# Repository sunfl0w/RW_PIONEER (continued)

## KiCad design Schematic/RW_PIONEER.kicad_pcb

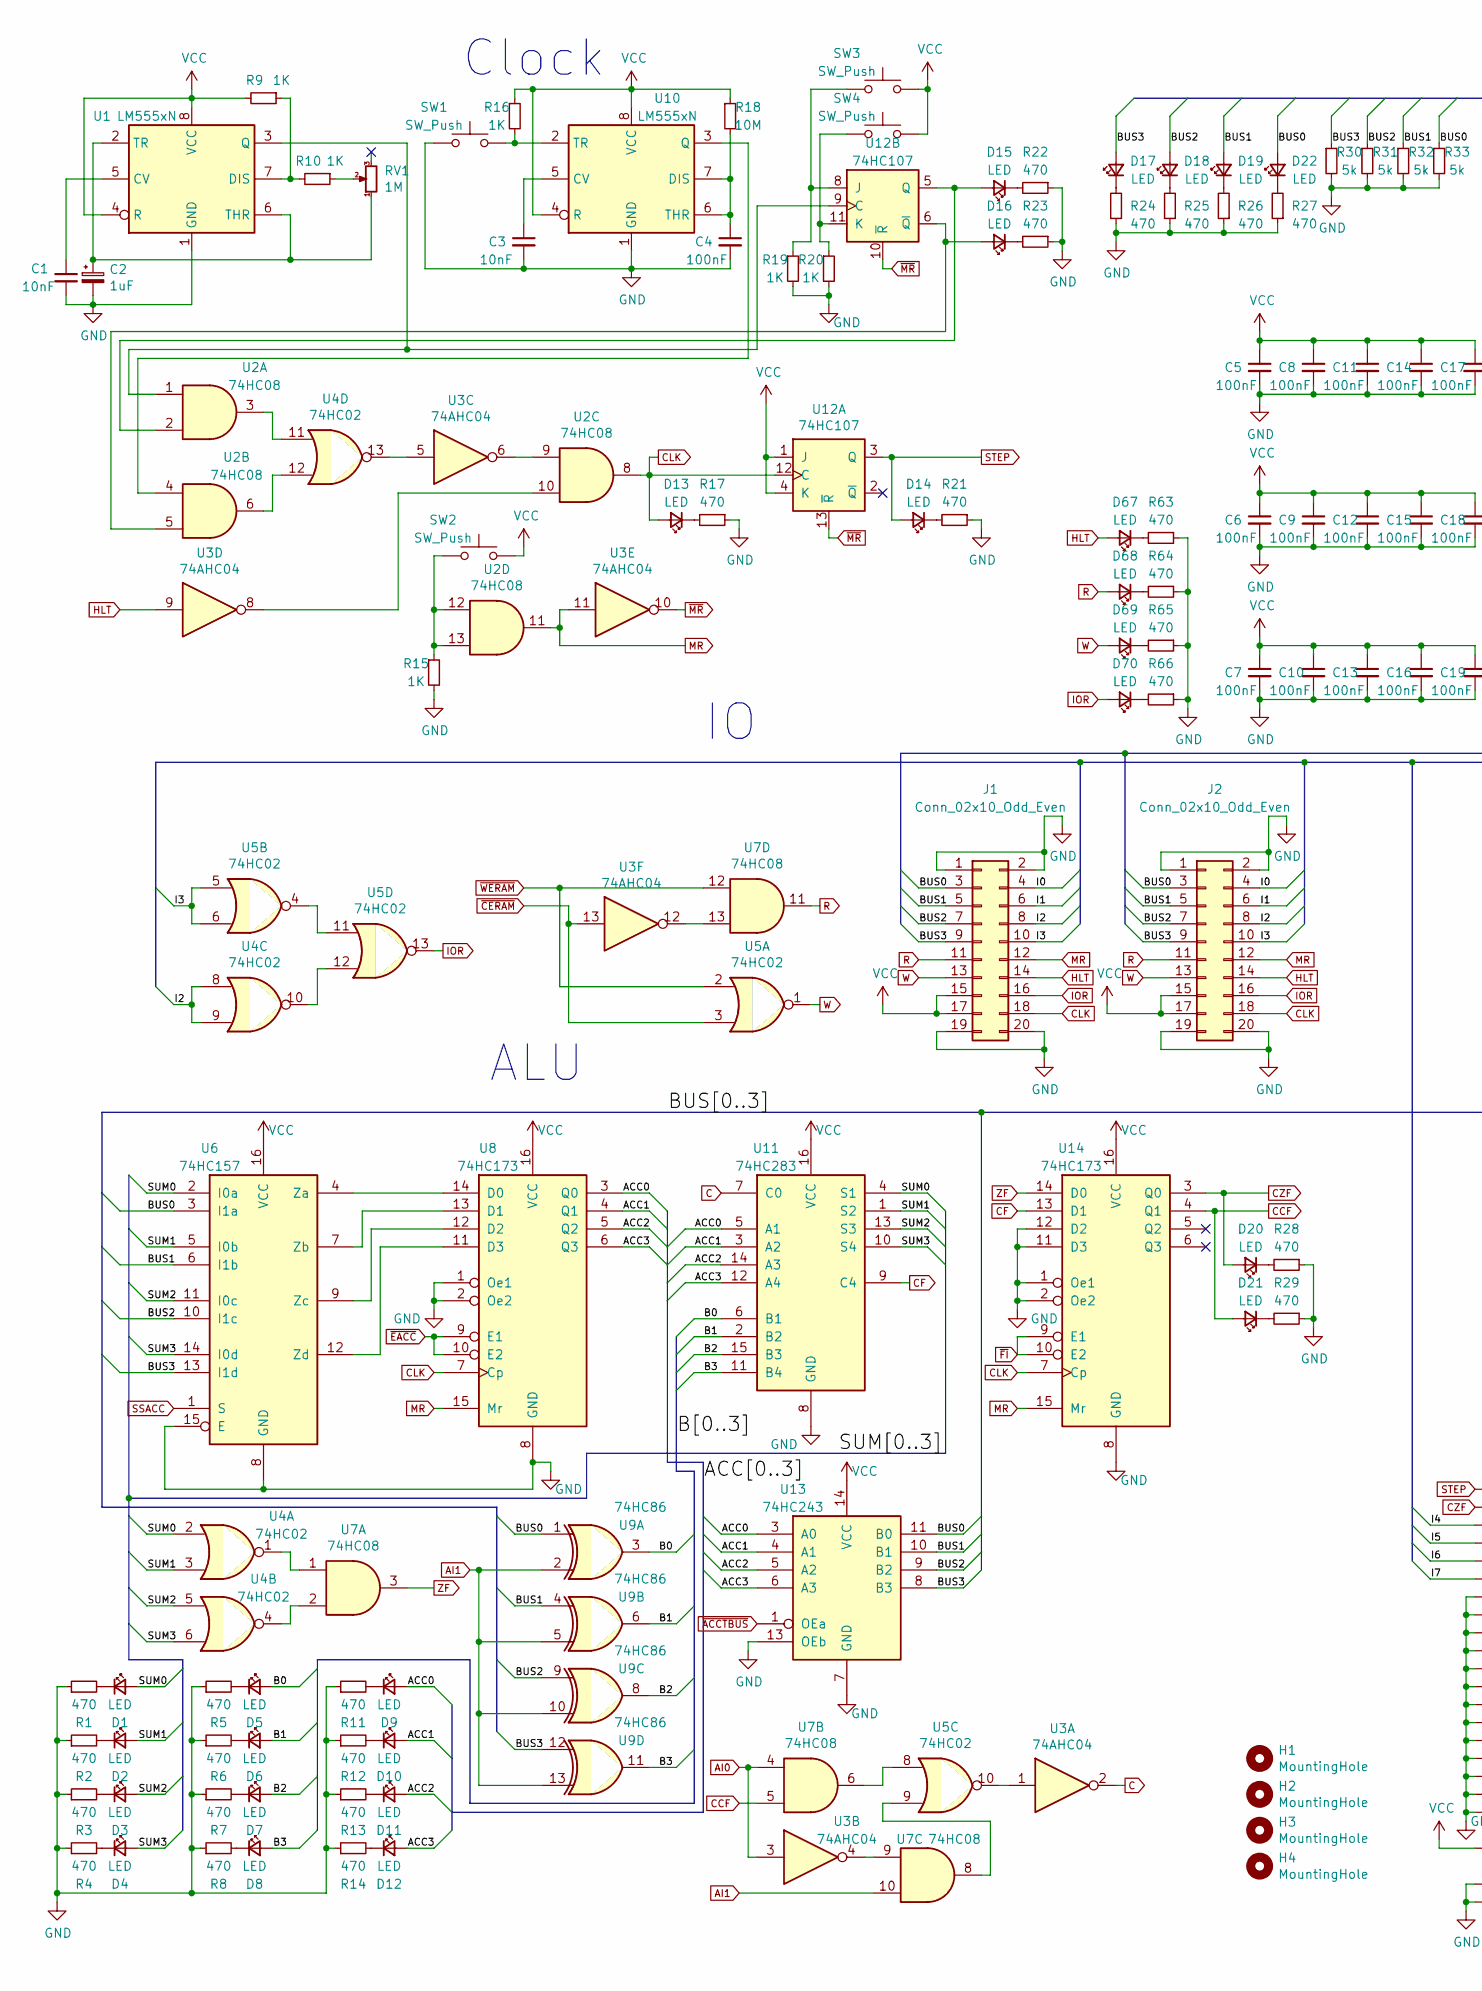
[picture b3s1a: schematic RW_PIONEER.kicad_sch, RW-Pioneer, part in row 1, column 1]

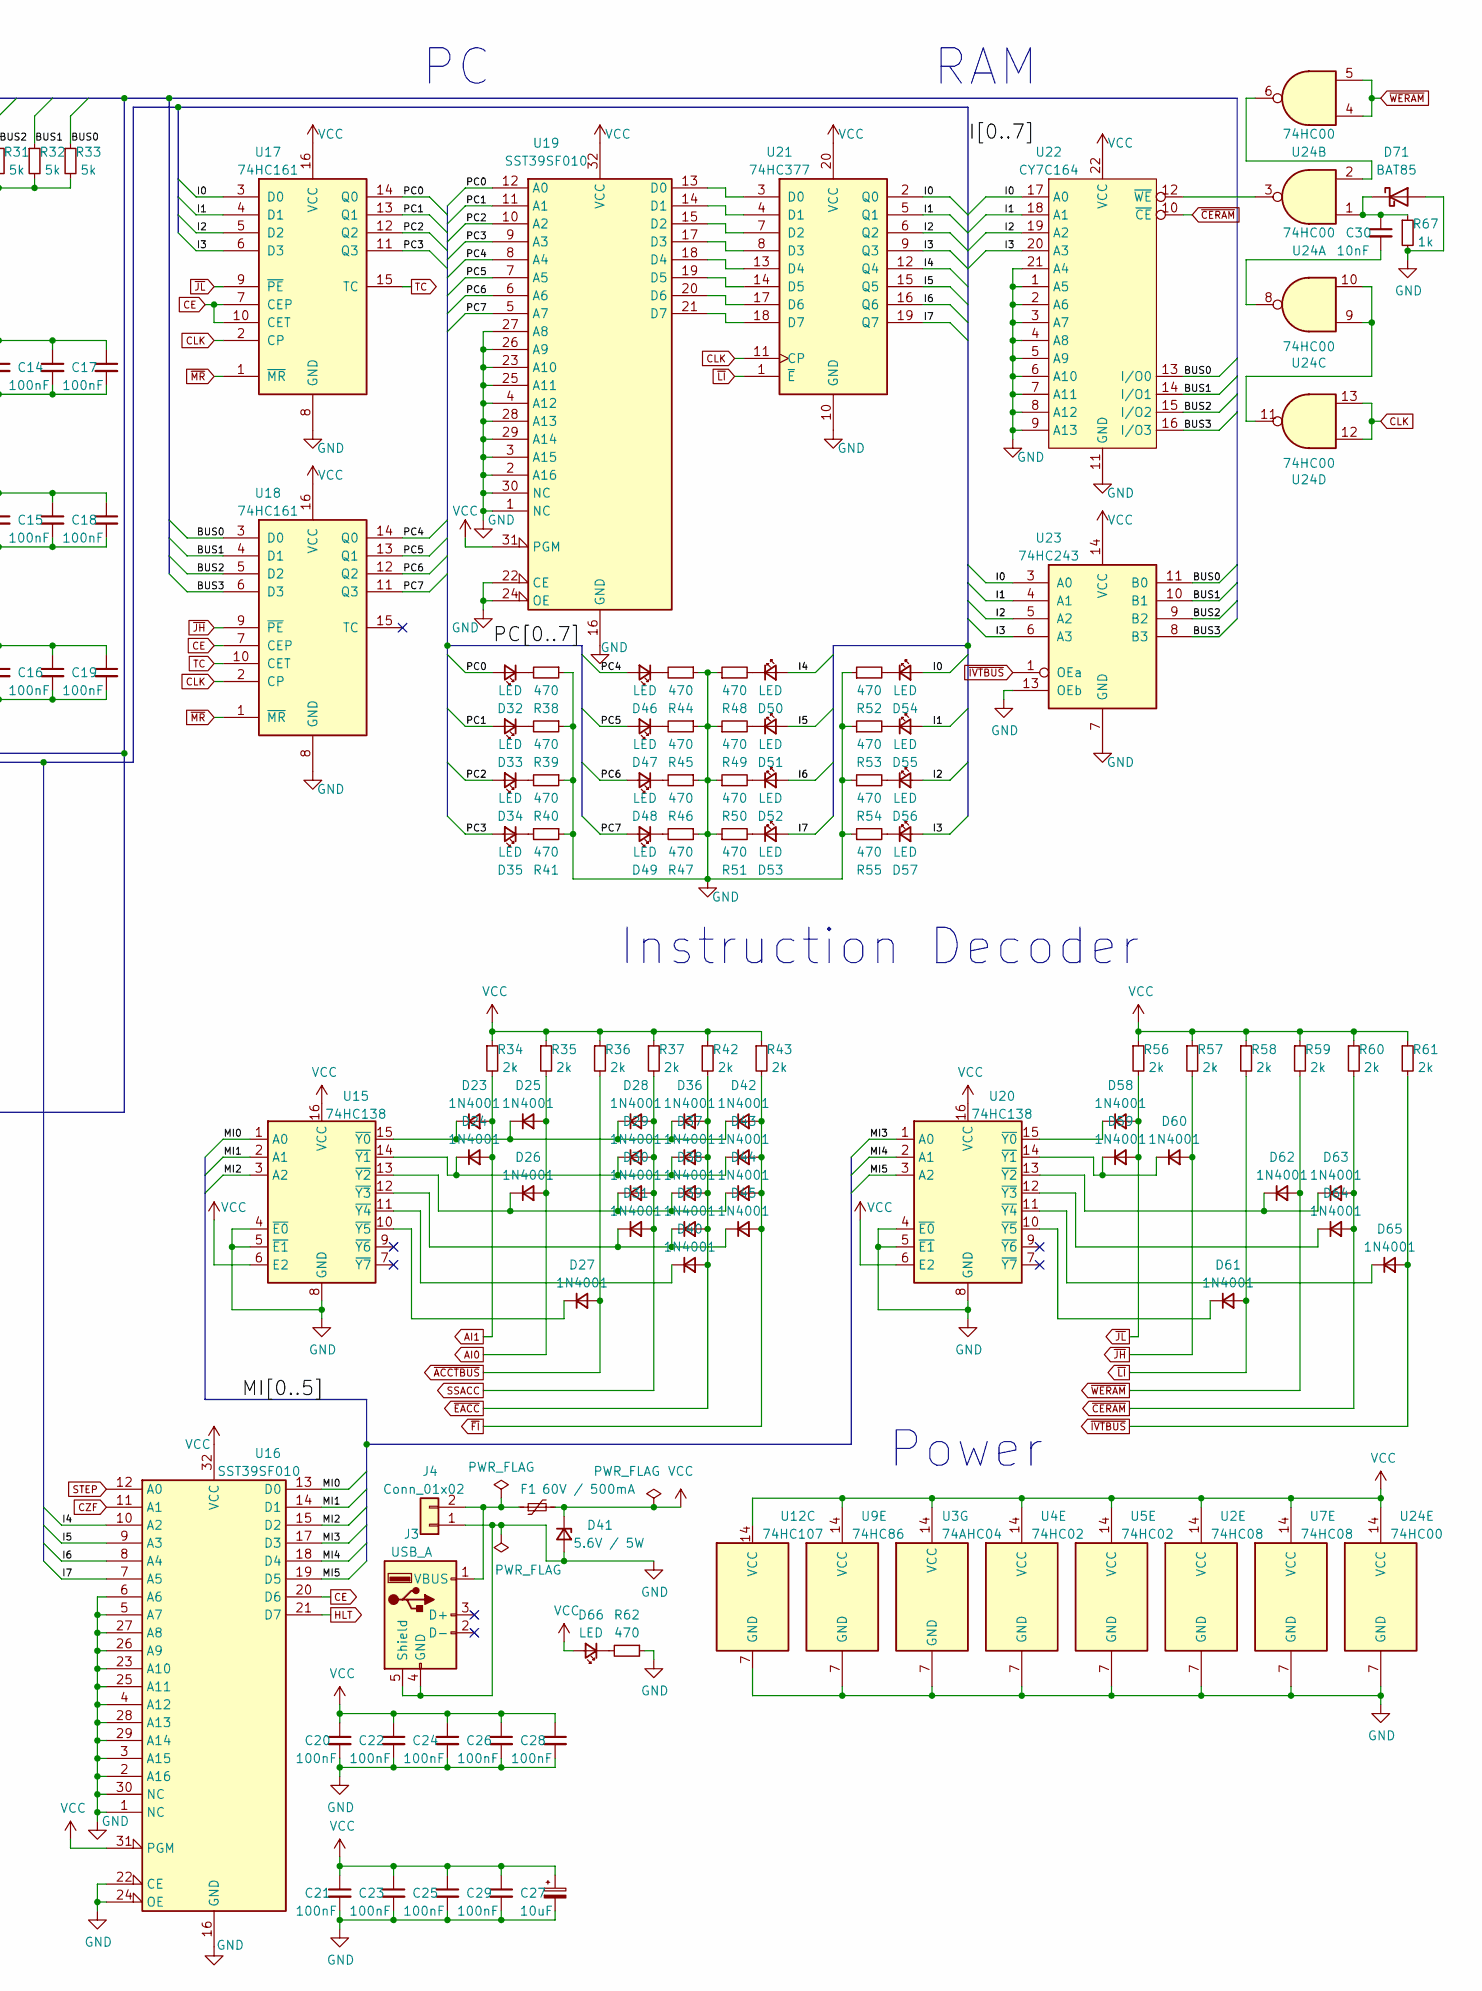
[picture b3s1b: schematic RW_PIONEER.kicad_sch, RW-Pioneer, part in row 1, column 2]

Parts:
C1, C3, C30: 10nF; C_Disc_D4.3mm_W1.9mm_P5.00mm
C2: 1uF; CP_Radial_D5.0mm_P2.50mm
C4, C5, C6, C7, C8, C9, C10, C11, C12, C13, C14, C15, C16, C17, C18, C19, C20, C21, C22, C23, C24, C25, C26, C28, C29: 100nF; C_Disc_D4.3mm_W1.9mm_P5.00mm
C27: 10uF; CP_Radial_D5.0mm_P2.50mm
D1, D2, D3, D4, D5, D6, D7, D8, D9, D10, D11, D12, D13, D14, D15, D16, D17, D18, D19, D20, D21, D22, D32, D33, D34, D35, D46, D47, D48, D49, D50, D51, D52, D53, D54, D55, D56, D57, D66, D67, D68, D69, D70: LED; LED_D5.0mm_Clear
D23, D24, D25, D26, D27, D28, D29, D30, D31, D36, D37, D38, D39, D40, D42, D43, D44, D45, D58, D59, D60, D61, D62, D63, D64, D65: 1N4001; D_DO-41_SOD81_P10.16mm_Horizontal
D41: 5.6V / 5W; D_DO-41_SOD81_P12.70mm_Horizontal
D71: BAT85; D_DO-35_SOD27_P7.62mm_Horizontal
F1: 60V / 500mA; R_Axial_DIN0207_L6.3mm_D2.5mm_P5.08mm_Vertical
H1, H2, H3, H4: MountingHole; MountingHole_3.2mm_M3
J1: Conn_02x10_Odd_Even; PinHeader_2x10_P2.54mm_Horizontal
J2: Conn_02x10_Odd_Even; IDC-Header_2x10_P2.54mm_Horizontal
J3: USB_A; USB_A_CONNFLY_DS1095-WNR0
J4: Conn_01x02; JST_XH_B2B-XH-A_1x02_P2.50mm_Vertical
R1, R2, R3, R4, R5, R6, R7, R8, R11, R12, R13, R14, R17, R21, R22, R23, R24, R25, R26, R27, R28, R29, R38, R39, R40, R41, R44, R45, R46, R47, R48, R49, R50, R51, R52, R53, R54, R55, R62, R63, R64, R65, R66: 470; R_Axial_DIN0207_L6.3mm_D2.5mm_P10.16mm_Horizontal
R9, R10, R15, R16, R19, R20: 1K; R_Axial_DIN0207_L6.3mm_D2.5mm_P10.16mm_Horizontal
R18: 10M; R_Axial_DIN0207_L6.3mm_D2.5mm_P10.16mm_Horizontal
R30, R31, R32, R33: 5k; R_Axial_DIN0207_L6.3mm_D2.5mm_P10.16mm_Horizontal
R34, R35, R36, R37, R42, R43, R56, R57, R58, R59, R60, R61: 2k; R_Axial_DIN0207_L6.3mm_D2.5mm_P10.16mm_Horizontal
R67: 1k; R_Axial_DIN0207_L6.3mm_D2.5mm_P10.16mm_Horizontal
RV1: 1M; Potentiometer_Piher_PT-10-H01_Horizontal
SW1, SW2, SW3, SW4: SW_Push; SW_PUSH_6mm
U1, U10: LM555xN; DIP-8_W7.62mm
U2, U7: 74HC08; DIP-14_W7.62mm
U3: 74AHC04; DIP-14_W7.62mm
U4, U5: 74HC02; DIP-14_W7.62mm
U6: 74HC157; DIP-16_W7.62mm
U8, U14: 74HC173; DIP-16_W7.62mm
U9: 74HC86; DIP-14_W7.62mm
U11: 74HC283; DIP-16_W7.62mm
U12: 74HC107; DIP-14_W7.62mm
U13, U23: 74HC243; DIP-14_W7.62mm
U15, U20: 74HC138; DIP-16_W7.62mm
U16, U19: SST39SF010; DIP-32_W15.24mm_Socket
U17, U18: 74HC161; DIP-16_W7.62mm
U21: 74HC377; DIP-20_W7.62mm
U22: CY7C164; DIP-22_W7.62mm
U24: 74HC00; DIP-14_W7.62mm

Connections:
/ACC0: D9.2 (A), U8.3 (Q0), U11.5 (A1), U13.3 (A0)
/ACC1: D10.2 (A), U8.4 (Q1), U11.3 (A2), U13.4 (A1)
/ACC2: D11.2 (A), U8.5 (Q2), U11.14 (A3), U13.5 (A2)
/ACC3: D12.2 (A), U8.6 (Q3), U11.12 (A4), U13.6 (A3)
/B0: D5.2 (A), U9.3, U11.6 (B1)
/B1: D6.2 (A), U9.6, U11.2 (B2)
/B2: D7.2 (A), U9.8, U11.15 (B3)
/B3: D8.2 (A), U9.11, U11.11 (B4)
/BUS0: D22.2 (A), J1.3, J2.3, R33.1, U6.3 (I1a), U9.1, U13.11 (B0), U18.3 (D0), U22.13 (I/O0), U23.11 (B0)
/BUS1: D19.2 (A), J1.5, J2.5, R32.1, U6.6 (I1b), U9.4, U13.10 (B1), U18.4 (D1), U22.14 (I/O1), U23.10 (B1)
/BUS2: D18.2 (A), J1.7, J2.7, R31.1, U6.10 (I1c), U9.9, U13.9 (B2), U18.5 (D2), U22.15 (I/O2), U23.9 (B2)
/BUS3: D17.2 (A), J1.9, J2.9, R30.1, U6.13 (I1d), U9.12, U13.8 (B3), U18.6 (D3), U22.16 (I/O3), U23.8 (B3)
/I0: D54.2 (A), J1.4, J2.4, U17.3 (D0), U21.2 (Q0), U22.17 (A0), U23.3 (A0)
/I1: D55.2 (A), J1.6, J2.6, U17.4 (D1), U21.5 (Q1), U22.18 (A1), U23.4 (A1)
/I2: D56.2 (A), J1.8, J2.8, U4.8, U4.9, U17.5 (D2), U21.6 (Q2), U22.19 (A2), U23.5 (A2)
/I3: D57.2 (A), J1.10, J2.10, U5.5, U5.6, U17.6 (D3), U21.9 (Q3), U22.20 (A3), U23.6 (A3)
/I4: D50.2 (A), U16.10 (A2), U21.12 (Q4)
/I5: D51.2 (A), U16.9 (A3), U21.15 (Q5)
/I6: D52.2 (A), U16.8 (A4), U21.16 (Q6)
/I7: D53.2 (A), U16.7 (A5), U21.19 (Q7)
/MI0: U15.1 (A0), U16.13 (D0)
/MI1: U15.2 (A1), U16.14 (D1)
/MI2: U15.3 (A2), U16.15 (D2)
/MI3: U16.17 (D3), U20.1 (A0)
/MI4: U16.18 (D4), U20.2 (A1)
/MI5: U16.19 (D5), U20.3 (A2)
/PC0: D32.2 (A), U17.14 (Q0), U19.12 (A0)
/PC1: D33.2 (A), U17.13 (Q1), U19.11 (A1)
/PC2: D34.2 (A), U17.12 (Q2), U19.10 (A2)
/PC3: D35.2 (A), U17.11 (Q3), U19.9 (A3)
/PC4: D46.2 (A), U18.14 (Q0), U19.8 (A4)
/PC5: D47.2 (A), U18.13 (Q1), U19.7 (A5)
/PC6: D48.2 (A), U18.12 (Q2), U19.6 (A6)
/PC7: D49.2 (A), U18.11 (Q3), U19.5 (A7)
/SUM0: D1.2 (A), U4.2, U6.2 (I0a), U11.4 (S1)
/SUM1: D2.2 (A), U4.3, U6.5 (I0b), U11.1 (S2)
/SUM2: D3.2 (A), U4.5, U6.11 (I0c), U11.13 (S3)
/SUM3: D4.2 (A), U4.6, U6.14 (I0d), U11.10 (S4)
AI0: D25.2 (A), D26.2 (A), R35.2, U3.3, U7.4
AI1: D23.2 (A), D24.2 (A), R34.2, U7.10, U9.2, U9.5, U9.10, U9.13
C: U3.2, U11.7 (C0)
CCF: D21.2 (A), U7.5, U14.4 (Q1)
CE: U16.20 (D6), U17.7 (CEP), U17.10 (CET), U18.7 (CEP)
CF: U11.9 (C4), U14.13 (D1)
CLK: D13.2 (A), J1.18, J2.18, U2.8, U8.7 (Cp), U12.12 (C), U14.7 (Cp), U17.2 (CP), U18.2 (CP), U21.11 (CP), U24.12, U24.13
CZF: D20.2 (A), U14.3 (Q0), U16.11 (A1)
GND: C1.2, C2.2, C3.2, C4.2, C5.2, C6.2, C7.2, C8.2, C9.2, C10.2, C11.2, C12.2, C13.2, C14.2, C15.2, C16.2, C17.2, C18.2, C19.2, C20.2, C21.2, C22.2, C23.2, C24.2, C25.2, C26.2, C27.2, C28.2, C29.2, D41.2 (A), D71.2 (A), J1.1, J1.2, J1.19, J1.20, J2.1, J2.2, J2.19, J2.20, J3.4 (GND), J3.5 (Shield), J4.1, R1.1, R2.1, R3.1, R4.1, R5.1, R6.1, R7.1, R8.1, R11.1, R12.1, R13.1, R14.1, R15.2, R17.1, R19.2, R20.2, R21.1, R22.1, R23.1, R24.1, R25.1, R26.1, R27.1, R28.1, R29.1, R30.2, R31.2, R32.2, R33.2, R38.1, R39.1, R40.1, R41.1, R44.1, R45.1, R46.1, R47.1, R48.1, R49.1, R50.1, R51.1, R52.1, R53.1, R54.1, R55.1, R62.1, R63.1, R64.1, R65.1, R66.1, R67.2, SW1.1, U1.1 (GND), U2.7 (GND), U3.7 (GND), U4.7 (GND), U5.7 (GND), U6.8 (GND), U6.15 (E), U7.7 (GND), U8.1 (Oe1), U8.2 (Oe2), U8.8 (GND), U9.7 (GND), U10.1 (GND), U11.8 (GND), U12.7 (GND), U13.7 (GND), U13.13 (OEb), U14.1 (Oe1), U14.2 (Oe2), U14.8 (GND), U14.11 (D3), U14.12 (D2), U15.4 (~E0), U15.5 (~E1), U15.8 (GND), U16.1 (NC), U16.2 (A16), U16.3 (A15), U16.4 (A12), U16.5 (A7), U16.6 (A6), U16.16 (GND), U16.22 (CE), U16.23 (A10), U16.24 (OE), U16.25 (A11), U16.26 (A9), U16.27 (A8), U16.28 (A13), U16.29 (A14), U16.30 (NC), U17.8 (GND), U18.8 (GND), U19.1 (NC), U19.2 (A16), U19.3 (A15), U19.4 (A12), U19.16 (GND), U19.22 (CE), U19.23 (A10), U19.24 (OE), U19.25 (A11), U19.26 (A9), U19.27 (A8), U19.28 (A13), U19.29 (A14), U19.30 (NC), U20.4 (~E0), U20.5 (~E1), U20.8 (GND), U21.10 (GND), U22.1 (A5), U22.2 (A6), U22.3 (A7), U22.4 (A8), U22.5 (A9), U22.6 (A10), U22.7 (A11), U22.8 (A12), U22.9 (A13), U22.11 (GND), U22.21 (A4), U23.7 (GND), U23.13 (OEb), U24.7 (GND)
HLT: D67.2 (A), J1.14, J2.14, U3.9, U16.21 (D7)
IOR: D70.2 (A), J1.16, J2.16, U5.13
MR: J1.12, J2.12, U2.11, U3.11, U8.15 (Mr), U14.15 (Mr)
unnamed: C30.2, U24.8
unnamed: D1.1 (K), R1.2
unnamed: D2.1 (K), R2.2
unnamed: D3.1 (K), R3.2
unnamed: D4.1 (K), R4.2
unnamed: D5.1 (K), R5.2
unnamed: D6.1 (K), R6.2
unnamed: D7.1 (K), R7.2
unnamed: D8.1 (K), R8.2
unnamed: D9.1 (K), R11.2
unnamed: D10.1 (K), R12.2
unnamed: D11.1 (K), R13.2
unnamed: D12.1 (K), R14.2
unnamed: D13.1 (K), R17.2
unnamed: D14.1 (K), R21.2
unnamed: D15.2 (A), U2.2, U12.5 (Q)
unnamed: D15.1 (K), R22.2
unnamed: D16.2 (A), U2.5, U12.6 (~Q)
unnamed: D16.1 (K), R23.2
unnamed: D17.1 (K), R24.2
unnamed: D18.1 (K), R25.2
unnamed: D19.1 (K), R26.2
unnamed: D20.1 (K), R28.2
unnamed: D21.1 (K), R29.2
unnamed: D22.1 (K), R27.2
unnamed: D23.1 (K), D25.1 (K), D28.1 (K), D36.1 (K), D42.1 (K), U15.15 (~Y0)
unnamed: D24.1 (K), D29.1 (K), D37.1 (K), D43.1 (K), U15.14 (~Y1)
unnamed: D26.1 (K), D30.1 (K), D38.1 (K), D44.1 (K), U15.13 (~Y2)
unnamed: D27.1 (K), U15.10 (~Y5)
unnamed: D31.1 (K), D39.1 (K), D45.1 (K), U15.12 (~Y3)
unnamed: D32.1 (K), R38.2
unnamed: D33.1 (K), R39.2
unnamed: D34.1 (K), R40.2
unnamed: D35.1 (K), R41.2
unnamed: D40.1 (K), U15.11 (~Y4)
unnamed: D46.1 (K), R44.2
unnamed: D47.1 (K), R45.2
unnamed: D48.1 (K), R46.2
unnamed: D49.1 (K), R47.2
unnamed: D50.1 (K), R48.2
unnamed: D51.1 (K), R49.2
unnamed: D52.1 (K), R50.2
unnamed: D53.1 (K), R51.2
unnamed: D54.1 (K), R52.2
unnamed: D55.1 (K), R53.2
unnamed: D56.1 (K), R54.2
unnamed: D57.1 (K), R55.2
unnamed: D58.1 (K), U20.15 (~Y0)
unnamed: D59.1 (K), D60.1 (K), U20.14 (~Y1)
unnamed: D61.1 (K), U20.10 (~Y5)
unnamed: D62.1 (K), D63.1 (K), U20.13 (~Y2)
unnamed: D64.1 (K), U20.12 (~Y3)
unnamed: D65.1 (K), U20.11 (~Y4)
unnamed: D66.1 (K), R62.2
unnamed: D67.1 (K), R63.2
unnamed: D68.1 (K), R64.2
unnamed: D69.1 (K), R65.2
unnamed: D70.1 (K), R66.2
unnamed: C30.1, D71.1 (K), R67.1, U24.1
unnamed: F1.1, J3.1 (VBUS), J4.2
unnamed: R10.1, RV1.2
unnamed: R15.1, SW2.1, U2.12, U2.13
unnamed: C1.1, U1.5 (CV)
unnamed: R9.1, R10.2, U1.7 (DIS)
unnamed: U1.3 (Q), U2.1, U12.9 (C)
unnamed: C2.1, RV1.1, U1.2 (TR), U1.6 (THR)
unnamed: U2.3, U4.11
unnamed: U2.6, U4.12
unnamed: U2.9, U3.6
unnamed: U2.10, U3.8
unnamed: U3.1, U5.10
unnamed: U3.4, U7.9
unnamed: U3.5, U4.13
unnamed: U3.12, U7.13
unnamed: U4.1, U7.1
unnamed: U4.4, U7.2
unnamed: U4.10, U5.12
unnamed: U5.8, U7.6
unnamed: U5.9, U7.8
unnamed: U5.4, U5.11
unnamed: U6.4 (Za), U8.14 (D0)
unnamed: U6.7 (Zb), U8.13 (D1)
unnamed: U6.9 (Zc), U8.12 (D2)
unnamed: U6.12 (Zd), U8.11 (D3)
unnamed: C3.1, U10.5 (CV)
unnamed: C4.1, R18.2, U10.6 (THR), U10.7 (DIS)
unnamed: U2.4, U10.3 (Q)
unnamed: R16.2, SW1.2, U10.2 (TR)
unnamed: R19.1, SW3.1, U12.8 (J)
unnamed: R20.1, SW4.1, U12.11 (K)
unnamed: U19.13 (D0), U21.3 (D0)
unnamed: U19.14 (D1), U21.4 (D1)
unnamed: U19.15 (D2), U21.7 (D2)
unnamed: U19.17 (D3), U21.8 (D3)
unnamed: U19.18 (D4), U21.13 (D4)
unnamed: U19.19 (D5), U21.14 (D5)
unnamed: U19.20 (D6), U21.17 (D6)
unnamed: U19.21 (D7), U21.18 (D7)
unnamed: U22.12 (~WE), U24.3
unnamed: U24.2, U24.6
unnamed: U24.9, U24.10, U24.11
R: D68.2 (A), J1.11, J2.11, U7.11
SSACC: D28.2 (A), D29.2 (A), D30.2 (A), D31.2 (A), R37.2, U6.1 (S)
STEP: D14.2 (A), U12.3 (Q), U16.12 (A0)
TC: U17.15 (TC), U18.10 (CET)
VCC: C5.1, C6.1, C7.1, C8.1, C9.1, C10.1, C11.1, C12.1, C13.1, C14.1, C15.1, C16.1, C17.1, C18.1, C19.1, C20.1, C21.1, C22.1, C23.1, C24.1, C25.1, C26.1, C27.1, C28.1, C29.1, D41.1 (K), D66.2 (A), F1.2, J1.15, J1.17, J2.15, J2.17, R9.2, R16.1, R18.1, R34.1, R35.1, R36.1, R37.1, R42.1, R43.1, R56.1, R57.1, R58.1, R59.1, R60.1, R61.1, SW2.2, SW3.2, SW4.2, U1.4 (R), U1.8 (VCC), U2.14 (VCC), U3.14 (VCC), U4.14 (VCC), U5.14 (VCC), U6.16 (VCC), U7.14 (VCC), U8.16 (VCC), U9.14 (VCC), U10.4 (R), U10.8 (VCC), U11.16 (VCC), U12.1 (J), U12.4 (K), U12.14 (VCC), U13.14 (VCC), U14.16 (VCC), U15.6 (E2), U15.16 (VCC), U16.31 (PGM), U16.32 (VCC), U17.16 (VCC), U18.16 (VCC), U19.31 (PGM), U19.32 (VCC), U20.6 (E2), U20.16 (VCC), U21.20 (VCC), U22.22 (VCC), U23.14 (VCC), U24.14 (VCC)
W: D69.2 (A), J1.13, J2.13, U5.1
ZF: U7.3, U14.14 (D0)
~ACCTBUS: D27.2 (A), R36.2, U13.1 (OEa)
~CERAM: D63.2 (A), D64.2 (A), R60.2, U3.13, U5.3, U22.10 (~CE)
~EACC: D36.2 (A), D37.2 (A), D38.2 (A), D39.2 (A), D40.2 (A), R42.2, U8.9 (E1), U8.10 (E2)
~FI: D42.2 (A), D43.2 (A), D44.2 (A), D45.2 (A), R43.2, U14.9 (E1), U14.10 (E2)
~IVTBUS: D65.2 (A), R61.2, U23.1 (OEa)
~JH: D60.2 (A), R57.2, U18.9 (~PE)
~JL: D58.2 (A), D59.2 (A), R56.2, U17.9 (~PE)
~LI: D61.2 (A), R58.2, U21.1 (~E)
~MR: U3.10, U12.10 (~R), U12.13 (~R), U17.1 (~MR), U18.1 (~MR)
~WERAM: D62.2 (A), R59.2, U5.2, U7.12, U24.4, U24.5

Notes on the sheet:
Clock
RAM
Power
ALU
Instruction Decoder

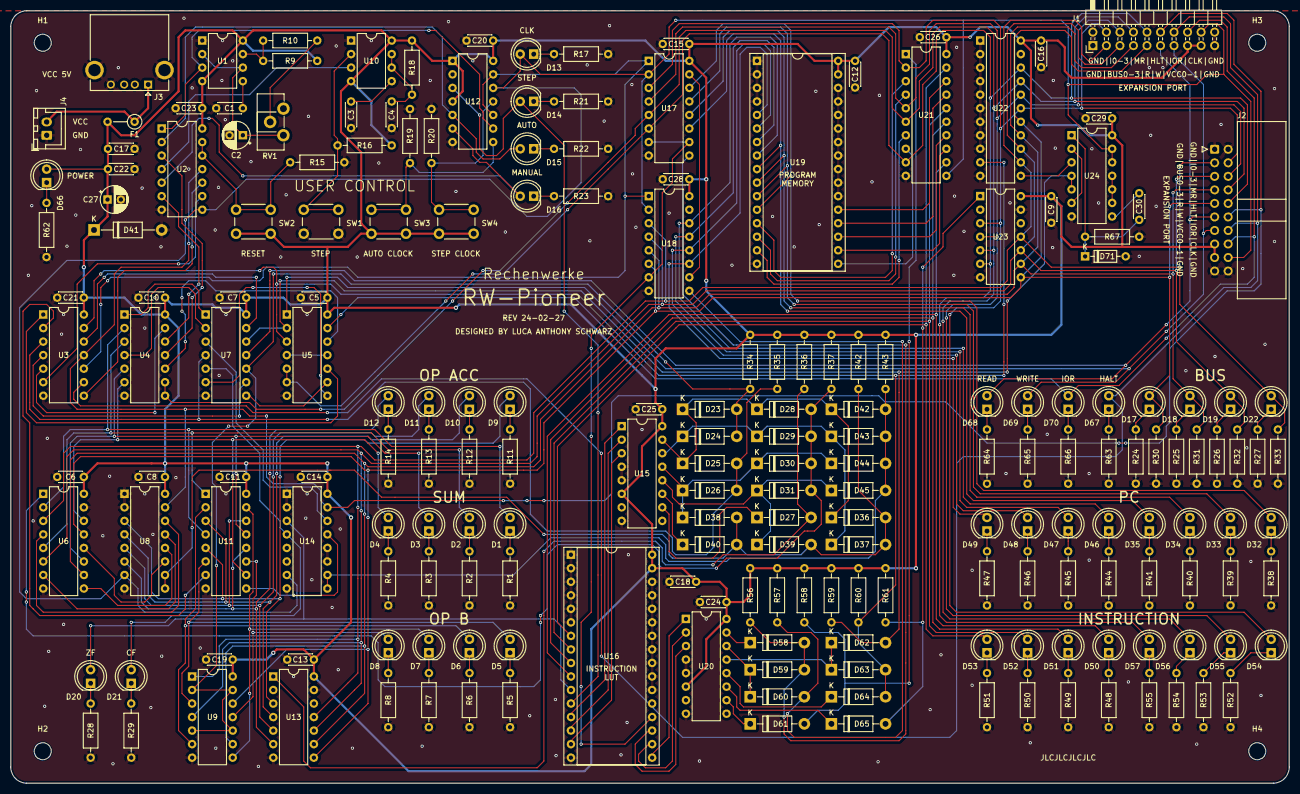
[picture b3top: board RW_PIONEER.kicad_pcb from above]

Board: 2 copper layers, 240.0 x 145.0 mm, 206 parts (0 on the bottom side), 168 nets.

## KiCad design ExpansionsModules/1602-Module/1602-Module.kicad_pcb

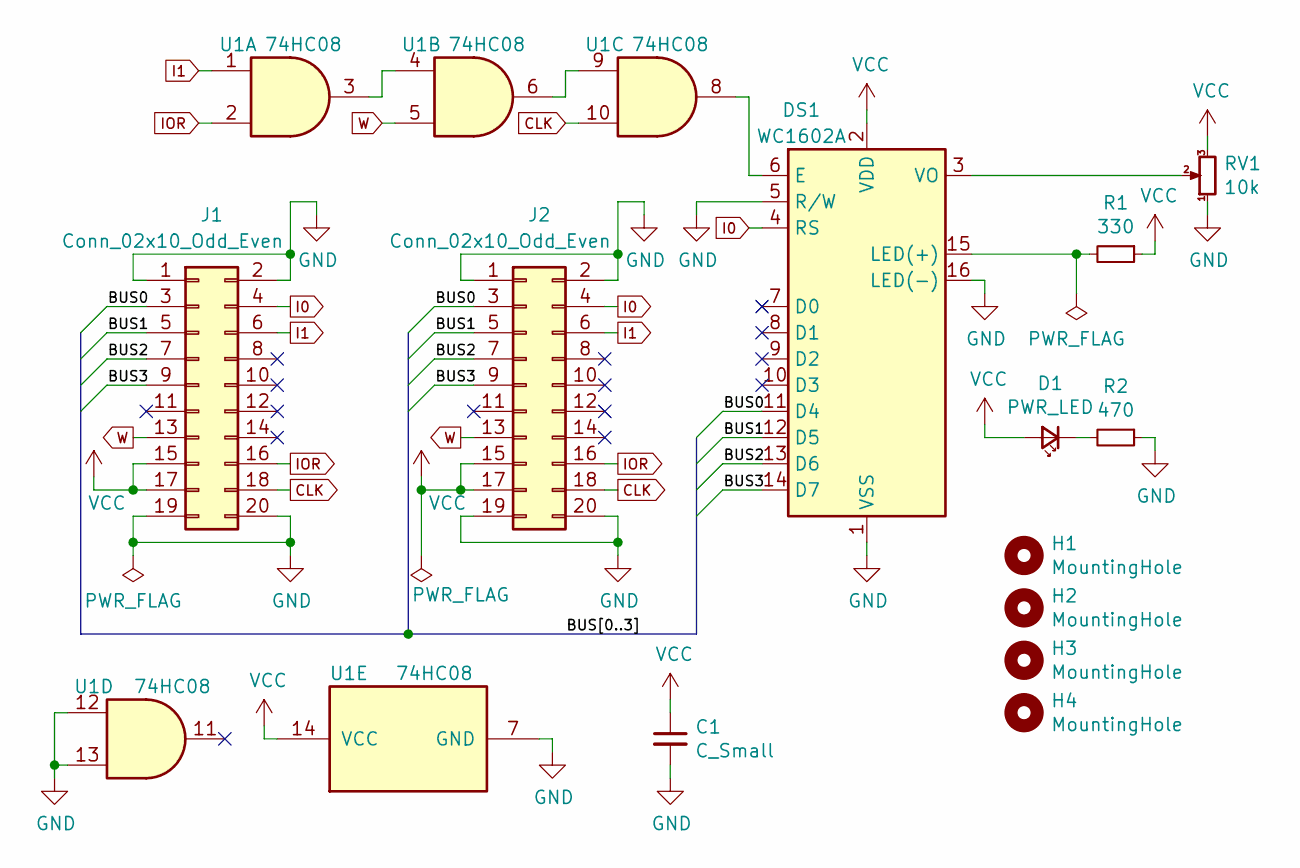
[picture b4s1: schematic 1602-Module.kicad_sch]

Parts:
C1: C_Small; C_Disc_D4.3mm_W1.9mm_P5.00mm
D1: PWR_LED; LED_D5.0mm_Clear
DS1: WC1602A
H1, H2, H3, H4: MountingHole; MountingHole_3.2mm_M3
J1: Conn_02x10_Odd_Even; IDC-Header_2x10_P2.54mm_Horizontal
J2: Conn_02x10_Odd_Even; PinSocket_2x10_P2.54mm_Horizontal
R1: 330; R_Axial_DIN0207_L6.3mm_D2.5mm_P10.16mm_Horizontal
R2: 470; R_Axial_DIN0207_L6.3mm_D2.5mm_P10.16mm_Horizontal
RV1: 10k; Potentiometer_Piher_PT-10-H01_Horizontal
U1: 74HC08; DIP-14_W7.62mm

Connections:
/BUS0: DS1.11 (D4), J1.3, J2.3
/BUS1: DS1.12 (D5), J1.5, J2.5
/BUS2: DS1.13 (D6), J1.7, J2.7
/BUS3: DS1.14 (D7), J1.9, J2.9
CLK: J1.18, J2.18, U1.10
GND: C1.2, DS1.1 (VSS), DS1.5 (R/W), DS1.16 (LED(-)), J1.1, J1.2, J1.19, J1.20, J2.1, J2.2, J2.19, J2.20, R2.1, RV1.1, U1.7 (GND), U1.12, U1.13
I0: DS1.4 (RS), J1.4, J2.4
I1: J1.6, J2.6, U1.1
IOR: J1.16, J2.16, U1.2
unnamed: D1.1 (K), R2.2
unnamed: DS1.3 (VO), RV1.2
unnamed: DS1.6 (E), U1.8
unnamed: DS1.15 (LED(+)), R1.2
unnamed: U1.3, U1.4
unnamed: U1.6, U1.9
VCC: C1.1, D1.2 (A), DS1.2 (VDD), J1.15, J1.17, J2.15, J2.17, R1.1, RV1.3, U1.14 (VCC)
W: J1.13, J2.13, U1.5

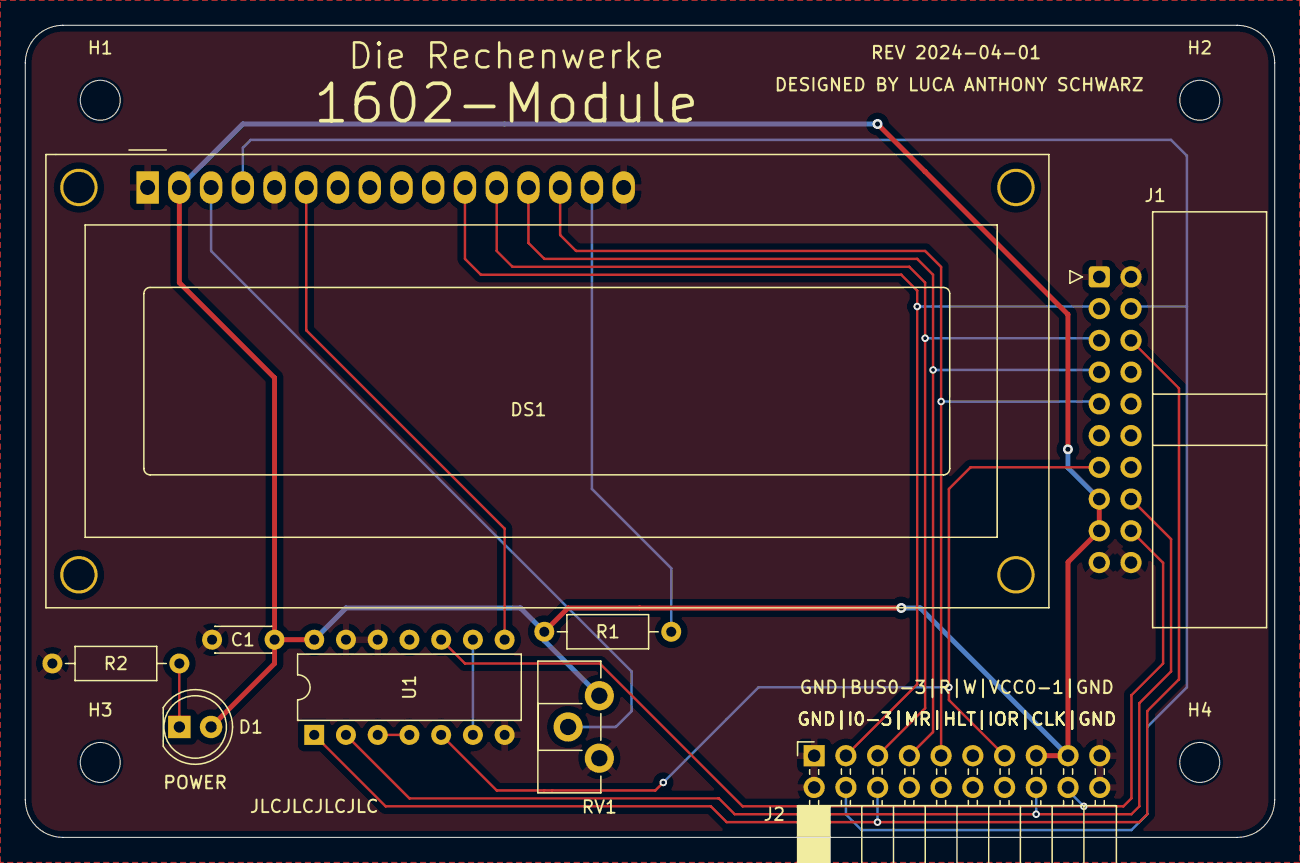
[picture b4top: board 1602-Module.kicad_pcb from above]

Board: 2 copper layers, 100.0 x 65.0 mm, 13 parts (0 on the bottom side), 17 nets.

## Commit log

2024-04-01 Add gitignore
2024-04-01 First commit of RW-Pioneer related material
2024-04-30 Added Verilog model. Added RWEMU. Added LUT generator. Updated README
